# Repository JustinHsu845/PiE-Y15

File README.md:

# Power Distribution Board
## Pioneers in Engineering Year 2022-2023
---
We are basing our design on the Y9 PDB design. We will use a toggle switch instead of the circuit breaker to power on the device, and a fuse in series with the battery as a safety feature. This is an effort to cut costs.  
  
**To Do:**  
- ~~Find toggle switch and make symbols and footprints~~
    - Use a rocker switch
- ~~Find fuse holders and make symbols and footprints~~
    - ~~Keystone Electronics through hole fuse holders~~ We found smd fuse holders
- ~~Setup staff bot and measure current draw under load to decide on fuse~~
    - 10A should be more than sufficient
    - Power switch more important
- ~~Determine number of ports necessary~~
    - 6 Anderson
    - 4 USB-A connectors (replacing molex)
- Figure out LED circuit (will handle with arduino (Pro Micro))
    - Need 1 green power on LED
        - On whenever power is entering the board.
    - Need 1 green 5v power LED
        - On when 5v power is working
    - ~~Need 1 low battery LED~~ Use Buzzer instead
        - On or flashing when any 1 cell is below 3.5 V (or something)
- Symbols and Footprints
    - Fuse Holder
    - Rocker Switch
    - ~~USB-A connector~~
    - ~~Pro Micro~~
    - Header Pins
    - ~~JST-XH~~
- Test ASAP
    - Main Power Distributor Circuit
    - Arduino LED circuit
    - Arduino Code
    - Make sure to add header pins to measure voltage from JST-XH plug
    - Use jumpers to connect between JST-XH and analog in

- Component Notes
    - Resistor for 12v LED dissipates 133mW at 590ohms, 15mA, and 530nm (green).
    https://jlcpcb.com/partdetail/liteon-LTSTC190TGKT/C364559
    - Resistor for 5v LED dissipates 27mW at 120ohms, 15mA, and 530nm (green).
    https://jlcpcb.com/partdetail/liteon-LTSTC190TGKT/C364559
    - R1 - R6 needs to be precise. Use tolerance < 0.1%. 0605 footprint. Dissipates max 3mW. Voltage divider scale down voltage by 4x. Each divider uses 0.1mA - 0.3mA

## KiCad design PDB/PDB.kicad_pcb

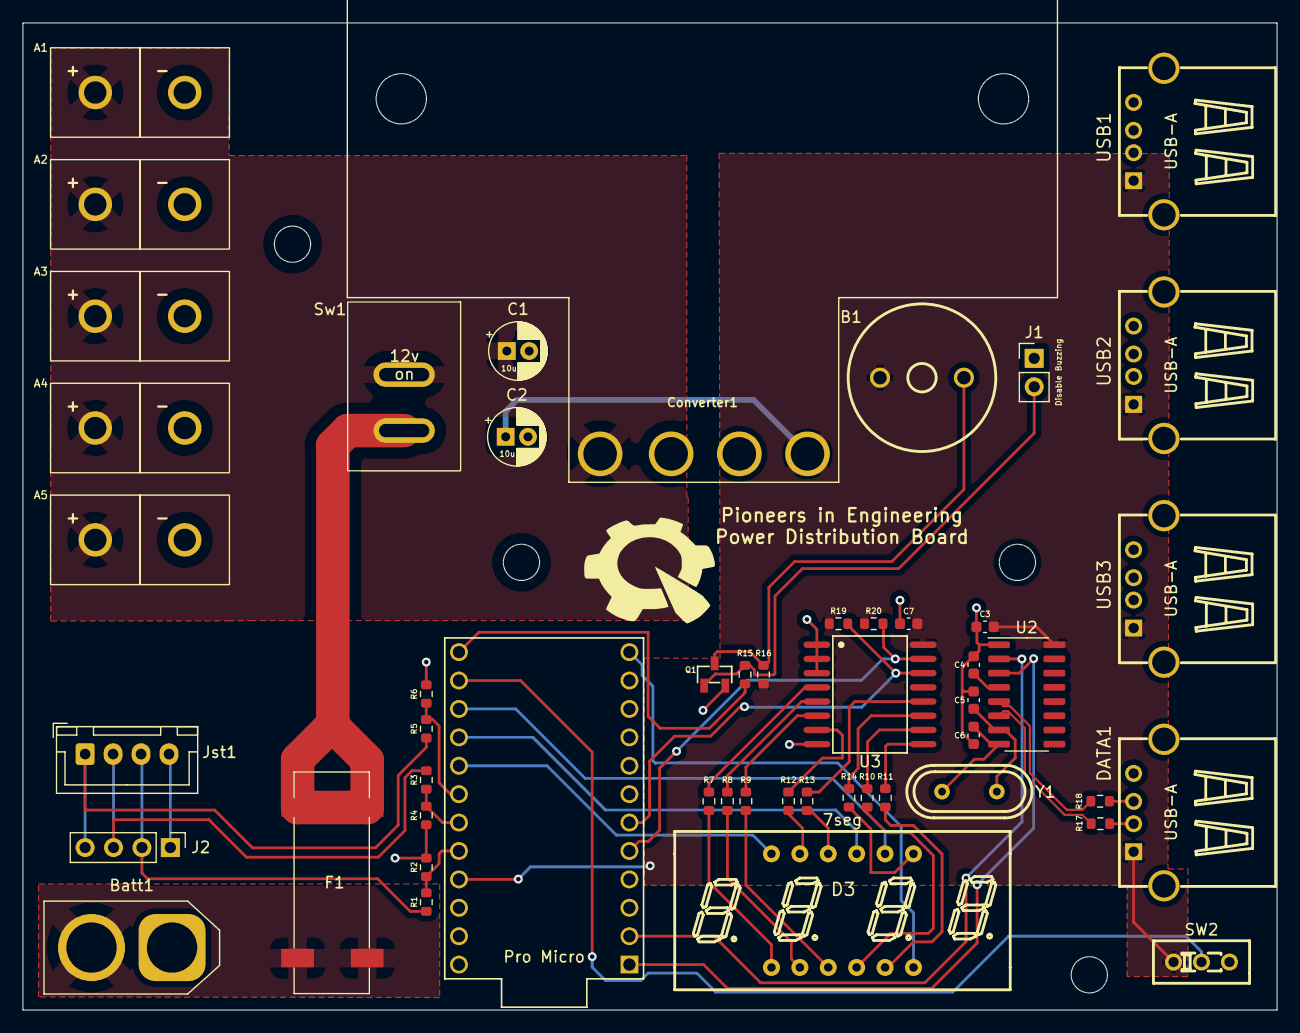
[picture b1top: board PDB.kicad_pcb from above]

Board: 2 copper layers, 112.1 x 88.3 mm, 51 parts (0 on the bottom side), 46 nets.

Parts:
A1, A2, A3, A4, A5: Anderson_Horizontal; anderson_horizontal
B1: Buzzer
Batt1: XT60_F; AMASS_XT60-M_1x02_P7.20mm_Vertical
C1, C2: 10u; CP_Radial_D5.0mm_P2.00mm
C3, C4: 0.1uF; C_0603_1608Metric
C5, C6: 22pF; C_0603_1608Metric
C7: 0.1u; C_0603_1608Metric
Converter1: BUCK_CONVERTER_5V; 5v_converter
D3: 4_digit_7_segment_display; LED-SEG-TH_12P-L30.0-W13.7-P2.54-S10.16-BL
DATA1: USB; USB-A_female
F1: Fuseholder; Fuse Holder SMD
J1: Conn_01x02; PinHeader_1x02_P2.54mm_Vertical
J2: Conn_01x04; PinHeader_1x04_P2.54mm_Vertical
Jst1: JST-XH_4-pin; JST_XH_B4B-XH-A_1x04_P2.50mm_Vertical
Pro1: ProMicro; ProMicro-EnforcedTop
Q1: s8050_JSMSEMI; s8050 JSMSEMI
R1, R3, R5: 30000; R_0603_1608Metric
R2, R4, R6: 10000; R_0603_1608Metric
R7, R8, R9, R10, R11, R12, R13, R14: 200; R_0603_1608Metric
R15: 3300; R_0603_1608Metric
R16: 1000; R_0603_1608Metric
R17, R18: 22; R_0603_1608Metric
R19, R20: 4700; R_0603_1608Metric
SW2: SW_SPDT; DEALON SS-12D01-G3
Sw1: D-SWITCH_MR5-111-C5N-BB; Rocker Switch
U2: CH340G; CH340g
U3: PCF8574; PCF8574T
USB1, USB2, USB3: USB; USB-A_female
Y1: 12MHz; JYJE S1C12000VWFAC

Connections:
/5v: B1.1 (input), C2.1, C3.1, C7.2, Converter1.1 (OUT+), DATA1.1 (VCC), Pro1.21 (VCC), R16.1, R19.1, R20.1, SW2.1 (A), U2.16 (VCC), U3.16 (VDD), USB1.1 (VCC), USB2.1 (VCC), USB3.1 (VCC)
/12v: A1.2 (power), A2.2 (power), A3.2 (power), A4.2 (power), A5.2 (power), C1.1, Converter1.4 (IN+), Sw1.2 (Out)
/A: R12.1, U3.7 (P3)
/B: R14.1, U3.11 (P6)
/Buzzer: Pro1.13 (10), R15.1
/C: R10.2, U3.10 (P5)
/Cell1: J2.2, Jst1.3 (Pin_1), R1.1
/Cell1+2: J2.3, Jst1.2, R3.1
/Cell1+2+3: J2.4, Jst1.1 (Pin_3), R5.2
/Cell1+2+3_s: Pro1.18 (A1), R5.1, R6.1
/Cell1+2_s: Pro1.19 (A2), R3.2, R4.2
/Cell1_s: Pro1.20 (A3), R1.2, R2.1
/D: R8.2, U3.5 (P1)
/D+: R18.1, U2.5 (UD+)
/D-: R17.1, U2.6 (UD-)
/DP: R9.2, U3.6 (P2)
/Dig1: D3.12 (Dig1), Pro1.17 (A0)
/Dig2: D3.9 (Dig2), Pro1.16 (15)
/Dig3: D3.8 (Dig3), Pro1.15 (14)
/Dig4: D3.6 (Dig4), Pro1.12 (9)
/E: R7.2, U3.4 (P0)
/F: R13.1, U3.12 (P7)
/G: R11.2, U3.9 (P4)
/Rx: Pro1.2 (RX), U2.2 (TXD)
/SCL: Pro1.6 (3), R19.2, U3.14 (SCL)
/SDA: Pro1.5 (2), R20.2, U3.15 (SDA)
/Tx: Pro1.1 (TX), U2.3 (RXD)
/base: J1.2, Q1.1 (B), R15.2
/battery: Batt1.2 (power), F1.1 (in1), F1.2 (in2)
/collector: B1.2 (output), Q1.3 (C), R16.2
/fuse out: F1.3 (out1), F1.4 (out2), Sw1.1 (In)
/toggle: Pro1.14 (16), SW2.2 (B)
GND: A1.1 (ground), A2.1 (ground), A3.1 (ground), A4.1 (ground), A5.1 (ground), Batt1.1 (ground), C1.2, C2.2, C3.2, C4.2, C5.2, C6.2, C7.1, Converter1.2 (OUT-), Converter1.3 (IN-), DATA1.4 (GND), DATA1.5 (Shield), DATA1.6 (Shield), J1.1, J2.1, Jst1.4 (GND), Pro1.3 (GND), Pro1.4 (GND), Pro1.23 (GND), Q1.2 (E), R2.2, R4.1, R6.2, SW2.3 (C), U2.1 (GND), U3.1 (A0), U3.2 (A1), U3.3 (A2), U3.8 (VSS), USB1.4 (GND), USB1.5 (Shield), USB1.6 (Shield), USB2.4 (GND), USB2.5 (Shield), USB2.6 (Shield), USB3.4 (GND), USB3.5 (Shield), USB3.6 (Shield)
unnamed: C4.1, U2.4 (V3)
unnamed: C5.1, U2.7 (XI), Y1.1
unnamed: C6.1, U2.8 (XO), Y1.2
unnamed: D3.1 (E), R7.1
unnamed: D3.2 (D), R8.1
unnamed: D3.3 (DP), R9.1
unnamed: D3.4 (C), R10.1
unnamed: D3.5 (G), R11.1
unnamed: D3.7 (B), R14.2
unnamed: D3.10 (F), R13.2
unnamed: D3.11 (A), R12.2
unnamed: DATA1.2 (D-), R17.2
unnamed: DATA1.3 (D+), R18.2

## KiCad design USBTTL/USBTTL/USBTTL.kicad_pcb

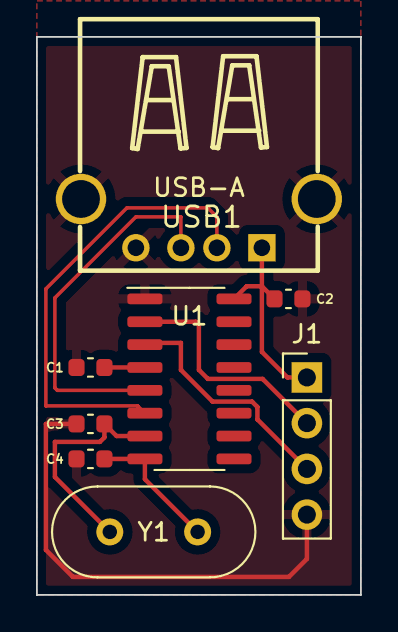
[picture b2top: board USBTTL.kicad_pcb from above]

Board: 2 copper layers, 18.0 x 31.0 mm, 8 parts (0 on the bottom side), 9 nets.

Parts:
C1, C2: 0.1uF; C_0603_1608Metric
C3, C4: 22pF; C_0603_1608Metric
J1: Conn_01x04; PinHeader_1x04_P2.54mm_Vertical
U1: CH340G; SOIC-16_3.9x9.9mm_P1.27mm
USB1: USB_Type_A_903-331A1011D10100; USB-A_female
Y1: 12MHz; Crystal_HC49-U_Vertical

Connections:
/5v: C2.1, J1.1, U1.16 (VCC), USB1.1 (VCC)
/D+: U1.5 (UD+), USB1.3 (D+)
/D-: U1.6 (UD-), USB1.2 (D-)
GND: C1.2, C2.2, C3.2, C4.2, J1.4, U1.1 (GND), USB1.4 (GND), USB1.5 (Shield), USB1.6 (Shield)
unnamed: J1.2, U1.2 (TXD)
unnamed: J1.3, U1.3 (RXD)
unnamed: C1.1, U1.4 (V3)
unnamed: C3.1, U1.7 (XI), Y1.1
unnamed: C4.1, U1.8 (XO), Y1.2

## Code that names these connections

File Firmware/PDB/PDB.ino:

#include <Wire.h>

#define expander B0100000 //hardwired ID of the expander

#define D1 A0
#define D2 15
#define D3 14
#define D4 9
#define BUZZER 10
#define Cell1 A3
#define Cell2 A2
#define Cell3 A1
#define TOGGLE 16
#include "array.h"
#include "functions.h"

void setup() {     
  //Serial.begin(9600);   
  Serial1.begin(9600); //Use serial1 to print out through tx/rx and FTDI chip to USB-A  

  pinMode(D1, OUTPUT);  
  pinMode(D2, OUTPUT);  
  pinMode(D3, OUTPUT);  
  pinMode(D4, OUTPUT); 

  pinMode(A3, INPUT);
  pinMode(A2, INPUT);
  pinMode(A1, INPUT);
  
  pinMode(BUZZER, OUTPUT);

  pinMode(TOGGLE, OUTPUT);

  pinMode(0, OUTPUT);
  pinMode(1, INPUT);
  
  Wire.begin();

  displayString("iiii", 1000);
  reset();
  tone(BUZZER, 440);
  delay(500);  
  noTone(BUZZER);
  delay(1000);
}

char network_switch = -1;
float ref = 5.16;

void loop() {
  float r_v1 = average(Cell1, 50);
  float v_v1 = r_v1 * (4*ref)/1023.0;
  String o_v1 = DisplayChars(String(v_v1));
  
  float r_v2 = average(Cell2, 50);
  float v_v2 = (r_v2 * (4*ref)/1023.0) - v_v1;
  String o_v2 = DisplayChars(String(v_v2));
  
  float r_v3 = average(Cell3, 50);
  float v_v3 = (r_v3 * (4*ref)/1023.0) - v_v2 - v_v1;
  String o_v3 = DisplayChars(String(v_v3));
  
  float r_all = average(Cell3, 50);
  float v_all = r_v3 * (4*ref)/1023.0;
  String o_all = DisplayChars(String(v_all));

  if (v_all < 11.5 || v_v1 < 3.8 || v_v2 < 3.8 || v_v3 < 3.8) {
    tone(10, 800);
  } else if (v_all > 12 && v_v1 > 4.0 && v_v2 > 4.0 && v_v3 > 4.0) {
    noTone(BUZZER);
  }
  
  Serial.println(digitalRead(TOGGLE));
  
  displayString("CEL1", 2000);
  displayString(o_v1, 2000);
  displayString("CEL2", 2000);
  displayString(o_v2, 2000);
  displayString("CEL3", 2000);
  displayString(o_v3, 2000);
  displayString("ALL ", 2000);
  displayString(o_all, 2000);
  /*
  int value = analogRead(Cell3);
  float voltage = value * (4*ref/1023);
  String voltage_s = DisplayChars(String(voltage));
  String ref_s = DisplayChars(String(ref));
  displayString("CEL3", 500);
  displayString(voltage_s, 500);
  displayString("4444", 500);
  displayString(ref_s, 500);
  if (voltage > 2.5) { //We will input 2.5v, should read 511 or 512
    ref -= 0.01;
  } else if (voltage < 2.5) {
    ref += 0.01;
  }
  */
}

void displayString(String phrase, int length) {
  for (int i = 0; i < length/8; i++) {

/*  This code controls what is output when the network switch is flipped.
    This will poll approximately once every 5 ms. */
    if (digitalRead(TOGGLE) != network_switch) {
      network_switch = digitalRead(TOGGLE);
      Serial1.println(digitalRead(TOGGLE));
    }


    printDigit(phrase[0], D1);
    delay(1);
    printDigit(phrase[1], D2);
    delay(1);
    printDigit(phrase[2], D3);
    delay(1);
    printDigit(phrase[3], D4);
    delay(1);
  }
}


/* gets the average values from an analog pin.
   Returns the averaged value of the pin. */
float average(int pin, int samples) {
  float sum = 0.0;
  for (int i = 0; i < samples; i++) {
    sum += analogRead(pin);
  }
  float average = sum / samples;
  return average;
}

void expanderWrite(byte _data) {
  Wire.beginTransmission(expander);
  Wire.write(_data);
  Wire.endTransmission(); 
}

void reset() { 
  digitalWrite(D1, LOW);
  digitalWrite(D2, LOW);
  digitalWrite(D3, LOW);
  digitalWrite(D4, LOW);
  expanderWrite(0b11111111);
}

int printDigit(char Chara, int digitPort) { 
  reset(); 
  int character = -1;
  digitalWrite(digitPort, HIGH);
  for(int i = 0 ; i < charsInArray ; i++) {
    if (Chara == Char[i][1]) {
     character = i;
    }
  }
  expanderWrite(~Char[character][0]);
}

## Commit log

2022-10-31 added short desc to README.md
2022-10-31 add README.md
2022-10-31 obsolete README.md
2022-11-02 started schematic
2022-11-02 Drafted battery indicator, added libraries
2022-11-05 Added anderson connector horizontal
2022-11-05 added pdb backups
2022-11-06 Put andersons on PCB, decoup cap needs footprint
2022-11-06 Fixed polarity of anderson_horizontal footprint
2022-11-06 Fixed XT60_F symbol contact locations
2022-11-07 added footprint to de cap
2022-11-07 made f.fab lines thicker with concern to JLC design rules
2022-11-07 sync 1172022
2022-11-07 added 5v rail and molex connectors
2022-11-07 added gitignore
2022-11-08 added Converter symbol/footprint
2022-11-08 gitignore updated
2022-11-08 Added to-dos
2022-11-15 updated to-dos
2022-11-15 updated schematic
2022-11-22 firmware for 7seg display
2022-11-22 Updated PDB with USB, battery sense
2022-11-22 added promicro
2022-11-23 started working on displaying decimal
2022-11-24 added arduino-cli
2022-11-24 cleaned up array.h
2022-11-25 Finished decimal point code
2022-11-29 Finished 7Seg display
2022-11-29 added symbols
2022-11-29 added usb, 7seg footprints
2022-11-30 fixed 5v pin on promicro symbol
2022-11-30 added resistors to common anode
2022-12-01 Fixed remove_char
2022-12-01 shortened printDisplay code
2022-12-01 adding autosaved files
2022-12-16 don't remember what this update is?
2022-12-16 finished Schematic
2022-12-16 added rocker switch and fuse holder symbols
2022-12-16 updated with LED and precision resistor notes
2023-01-08 gonna actually do some work
2023-01-10 changed pin #
2023-01-10 Added order invoices
2023-01-10 Fixed seg dis and added buzzer amp circuit
2023-01-10 Fixed 7-seg and buzzer symbols to match 50 mil pin standard
2023-01-10 added datasheets
2023-01-11 added Buzzer, Fuseholder, Rocker Switch
2023-01-11 Fixed jst pins
2023-01-11 Started footprints
2023-01-12 Put most components on board
2023-01-12 added footprint for s8050 smd
2023-01-13 Completed board layout
2023-01-13 I swear i didn't change anything
2023-01-13 fixed silkscreen clipped on usb-a female
2023-01-16 fixed pin numbers
2023-01-16 added FTDI chip
2023-01-16 Fixed USB Port
2023-01-16 USB-to-TTL adapter
2023-01-18 revised layout for smaller size
2023-01-18 Added + and - on silkscreen
2023-01-18 no idea what i changed here
2023-01-18 Started tracking
2023-01-18 Increased track size for USB
2023-01-26 added a bunch of footprints
2023-01-26 Finished board layout?
2023-01-26 added symbols i think
2023-01-26 added datasheets of components
2023-01-28 test ipad
2023-02-08 ordered this ****
2023-02-11 fixed PDB layout
2023-02-11 created production files
2023-02-11 added some invoices
2023-02-11 added team flag
2023-02-18 fixed all issues for this season
2023-06-19 Only PDB related stuff
2023-06-19 Readme for firmware
2023-07-23 Final commit
2023-10-05 idk when this was

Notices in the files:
PDB/PDB.kicad_pcb:
Copyright (c) 2023, Pioneers in Engineering
All rights reserved.
